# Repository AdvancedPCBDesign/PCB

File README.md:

# Advanced PCB Design (Group 15)

<a href="https://advancedpcbdesign.github.io/PCB/schematic.pdf"><strong>View Schematic (pdf) »</strong></a>

## KiCad Setup

### git

Execute in same directory as this README file

Before working on this project:
- `git pull`

See what's changed:
- `git status`

Commit and push changes:
- `git add *`
- `git commit -m "changes in ..."`
- `git push`

#### KiCAD JLCPCB tools
[https://github.com/bouni/kicad-jlcpcb-tools](https://github.com/bouni/kicad-jlcpcb-tools)

## Components Overview

| Concept                                         | Component             | Stock  | Price   | Link                                                                                                                                                                                                                                                                                                                                                                                                                                                                                                                                                                                                                                                                                                                                                                                                                                                                                                                                                                                                                                                                                                                                                                                                                                                                                                                                                              |
| ----------------------------------------------- | --------------------- | ------ | ------- | ----------------------------------------------------------------------------------------------------------------------------------------------------------------------------------------------------------------------------------------------------------------------------------------------------------------------------------------------------------------------------------------------------------------------------------------------------------------------------------------------------------------------------------------------------------------------------------------------------------------------------------------------------------------------------------------------------------------------------------------------------------------------------------------------------------------------------------------------------------------------------------------------------------------------------------------------------------------------------------------------------------------------------------------------------------------------------------------------------------------------------------------------------------------------------------------------------------------------------------------------------------------------------------------------------------------------------------------------------------------- |
| UV Sensor                                       | AS7331-AQFM           | 0      | $ 12.87 | [LCSC](https://www.lcsc.com/product-detail/C22457702.html) [Datasheet](https://www.lcsc.com/datasheet/C22457702.pdf)                                                                                                                                                                                                                                                                                                                                                                                                                                                                                                                                                                                                                                                                                                                                                                                                                                                                                                                                                                                                                                                                                                                                                                                                                                              |
| UV Sensor I2C                                   | LTR-390UV-01          | 0      | $ 3.37  | [JLCPCB](https://jlcpcb.com/partdetail/LiteOn-LTR_390UV01/C492374) [Datasheet](https://jlc-prod-smt.oss-eu-central-1.aliyuncs.com/smtDataManualFile/8588894290253004800-C492374.pdf?response-content-disposition=attachment%3B%20filename%3DC492374.pdf%3B%20filename%2A%3DUTF-8%27%27C492374.pdf&x-oss-date=20261022T112244Z&x-oss-expires=1800&x-oss-security-token=CAISgAN1q6Ft5B2yfSjIr5nRJvvBhrhH9oOcYUHngWMsf%2B1F3Z3fqTz2IHhMdHJsAOodtv0%2FmmhT6PkclqRLcbhpcmfjV%2BZHzLB8qfkBhX8%2F557b16cNrbH4M4H6aXeirtuwDsz9SNTCALjPD3nPii50x5bjaDymRCbLGJaViJlhHLN1Ow6jdmhpCctxLAlvo9NgFxm3D%2Fu2NQPwiWf9FVdhvhEG6Vly8qOi2MaRmFy8yFTx0b0SvJ%2BjYMrmPctoN9JnSdC5mfdzau3a1TJ84gRD0a5wkaVA1zbDs5bfISEIuUzebreLqY03dV4mOvdqIcMe8qigz88fk%2FfIioH6xyxKOexoSCnFTOiiupCcQLPyao9jLu6iayqViY7QaIOTqQohZmkAMwVOasAsI3Ngh4zF97Qt0cVNkXO9gWfLI8DtuMleWmrJ0EBmoaHD0eS19jklBdzSlusJRAJJUVBflCeKEaRNSAd3WGhEfM2%2BBt4QT30w5N2u00S8OSMIl8lOFKKWD5sagAFtcwKG348b1mUzBgtJh4%2BMkQ0MNsn9%2FxF2HpGh0Bm3%2BAHDdCkBsMSQTkxhfpKD557V3bFmR%2FM6RO7ja6TD2TNMN4imTTkpyuXGCddEgNZONk%2FHSSW0lGRNfjN74gcBhU2Y56%2FkgDQhi0Zqyy4%2BQfrkimxCRkldHE8glM%2BFpMkIFiAA&x-oss-signature-version=OSS4-HMAC-SHA256&x-oss-credential=STS.NZdmAukgfAAwcgVecysbi2XtK%2F20261022%2Feu-central-1%2Foss%2Faliyun_v4_request&x-oss-signature=278c7b70a0f79256bc8ae240f49d7be2213cf88d3748ce308f11e6cd0a1ca70c)      |
| UV Sensor I2C                                   | Si1133                | 0      | $ 2.74  | [JLCPCB](https://jlcpcb.com/partdetail/SKYWORKS_SILICONLABS-SI1133_AA00GM/C3678545)                                                                                                                                                                                                                                                                                                                                                                                                                                                                                                                                                                                                                                                                                                                                                                                                                                                                                                                                                                                                                                                                                                                                                                                                                                                                               |
| Co2 Sensor                                      | SCD40-D-R1            | 389    | $ 15.70 | [JLCPCB](https://jlcpcb.com/partdetail/Sensirion-SCD40_DR1/C3037696) [Datasheet](https://jlc-prod-smt.oss-eu-central-1.aliyuncs.com/smtDataManualFile/8589837130307973120-C3037696.pdf?response-content-disposition=attachment%3B%20filename%3DC3037696.pdf%3B%20filename%2A%3DUTF-8%27%27C3037696.pdf&x-oss-date=20261022T112435Z&x-oss-expires=1800&x-oss-security-token=CAISgAN1q6Ft5B2yfSjIr5nRJvvBhrhH9oOcYUHngWMsf%2B1F3Z3fqTz2IHhMdHJsAOodtv0%2FmmhT6PkclqRLcbhpcmfjV%2BZHzLB8qfkBhX8%2F557b16cNrbH4M4H6aXeirtuwDsz9SNTCALjPD3nPii50x5bjaDymRCbLGJaViJlhHLN1Ow6jdmhpCctxLAlvo9NgFxm3D%2Fu2NQPwiWf9FVdhvhEG6Vly8qOi2MaRmFy8yFTx0b0SvJ%2BjYMrmPctoN9JnSdC5mfdzau3a1TJ84gRD0a5wkaVA1zbDs5bfISEIuUzebreLqY03dV4mOvdqIcMe8qigz88fk%2FfIioH6xyxKOexoSCnFTOiiupCcQLPyao9jLu6iayqViY7QaIOTqQohZmkAMwVOasAsI3Ngh4zF97Qt0cVNkXO9gWfLI8DtuMleWmrJ0EBmoaHD0eS19jklBdzSlusJRAJJUVBflCeKEaRNSAd3WGhEfM2%2BBt4QT30w5N2u00S8OSMIl8lOFKKWD5sagAFtcwKG348b1mUzBgtJh4%2BMkQ0MNsn9%2FxF2HpGh0Bm3%2BAHDdCkBsMSQTkxhfpKD557V3bFmR%2FM6RO7ja6TD2TNMN4imTTkpyuXGCddEgNZONk%2FHSSW0lGRNfjN74gcBhU2Y56%2FkgDQhi0Zqyy4%2BQfrkimxCRkldHE8glM%2BFpMkIFiAA&x-oss-signature-version=OSS4-HMAC-SHA256&x-oss-credential=STS.NZdmAukgfAAwcgVecysbi2XtK%2F20261022%2Feu-central-1%2Foss%2Faliyun_v4_request&x-oss-signature=192cf8a0d5a21bb1fca0288a9b8ef685442e7d2fc05deb0e38e5b62fed935ffc) |
| gas, pressure, temperature & humidity<br>sensor | BME680                | 372    | $ 10.86 | [JLCPCB](https://jlcpcb.com/partdetail/BoschSensortec-BME680/C125972) [Datasheet](https://jlc-prod-smt.oss-eu-central-1.aliyuncs.com/smtDataManualFile/8588886842028122112-C125972.pdf?response-content-disposition=attachment%3B%20filename%3DC125972.pdf%3B%20filename%2A%3DUTF-8%27%27C125972.pdf&x-oss-date=20261021T151906Z&x-oss-expires=1800&x-oss-security-token=CAISgAN1q6Ft5B2yfSjIr5mCf8%2FaupxQhLPSR0PwkFIwSsdZuKDbkjz2IHhMdHJsAOodtv0%2FmmhT6PkclqRLcbhpcmfjV%2BZHzLB8qZYVtxg8557b16cNrbH4M4H6aXeirtuwDsz9SNTCALjPD3nPii50x5bjaDymRCbLGJaViJlhHLN1Ow6jdmhpCctxLAlvo9NgFxm3D%2Fu2NQPwiWf9FVdhvhEG6Vly8qOi2MaRmFy8yFTx0b0SvJ%2BjYMrmPctoN9JnSdC5mfdzau3a1TJ84gRD0a5wkaVA1zbDs5bfISEIuUzebreLqY03dV4mOvdqIcMe8qigz88fk%2FfIioH6xyxKOexoSCnFTOiiupCcQLPyao9jLu6iayqViY7QaIOTqQohZmkAMwVOasAsI3Ngh4zF97Qt0cVNkXO9gWfLI8DtuMleWgqmD8h7waHD0eS19jklBdzSlusJRAJJUVBflCeKEaRNSAd3WGhEfM2%2BBt4QT30w5N2u00S8OSMIJCdatqKWD5sagAEv7ngkOgawgwfiUHBX47YDcRBsRJt1XfKQ06GKLNxnRZIJmWZTwc55WEkmHm69WrZcaDtwaaN51Z9kWhH1cAPyDc6chX00A9ff2085vDMjgJllAMLDfzRuJBN82j6JOFTTuQiaDRPYa2AWHEQ4EVaGZsqWWgurQIq0EPFC1YsBqiAA&x-oss-signature-version=OSS4-HMAC-SHA256&x-oss-credential=STS.NZ74unWCq3q9EeAtReFHuWepp%2F20261021%2Feu-central-1%2Foss%2Faliyun_v4_request&x-oss-signature=7137659a65947dfa91fdfa0ecc3feda6760c6ecd1cf832c23a8c38a2930725ed)                     |
| SPI Digital to Analog Converters (DAC)          | MCP4822-E/SN          | 2,766  | $ 2.37  | [JLCPCB](https://jlcpcb.com/partdetail/MicrochipTech-MCP4822_ESN/C16040) [Datasheet](https://jlc-prod-smt.oss-eu-central-1.aliyuncs.com/smtDataManualFile/8588882123877470208-C16040.pdf?response-content-disposition=attachment%3B%20filename%3DC16040.pdf%3B%20filename%2A%3DUTF-8%27%27C16040.pdf&x-oss-date=20261022T112911Z&x-oss-expires=1800&x-oss-security-token=CAISgAN1q6Ft5B2yfSjIr5nRJvvBhrhH9oOcYUHngWMsf%2B1F3Z3fqTz2IHhMdHJsAOodtv0%2FmmhT6PkclqRLcbhpcmfjV%2BZHzLB8qfkBhX8%2F557b16cNrbH4M4H6aXeirtuwDsz9SNTCALjPD3nPii50x5bjaDymRCbLGJaViJlhHLN1Ow6jdmhpCctxLAlvo9NgFxm3D%2Fu2NQPwiWf9FVdhvhEG6Vly8qOi2MaRmFy8yFTx0b0SvJ%2BjYMrmPctoN9JnSdC5mfdzau3a1TJ84gRD0a5wkaVA1zbDs5bfISEIuUzebreLqY03dV4mOvdqIcMe8qigz88fk%2FfIioH6xyxKOexoSCnFTOiiupCcQLPyao9jLu6iayqViY7QaIOTqQohZmkAMwVOasAsI3Ngh4zF97Qt0cVNkXO9gWfLI8DtuMleWmrJ0EBmoaHD0eS19jklBdzSlusJRAJJUVBflCeKEaRNSAd3WGhEfM2%2BBt4QT30w5N2u00S8OSMIl8lOFKKWD5sagAFtcwKG348b1mUzBgtJh4%2BMkQ0MNsn9%2FxF2HpGh0Bm3%2BAHDdCkBsMSQTkxhfpKD557V3bFmR%2FM6RO7ja6TD2TNMN4imTTkpyuXGCddEgNZONk%2FHSSW0lGRNfjN74gcBhU2Y56%2FkgDQhi0Zqyy4%2BQfrkimxCRkldHE8glM%2BFpMkIFiAA&x-oss-signature-version=OSS4-HMAC-SHA256&x-oss-credential=STS.NZdmAukgfAAwcgVecysbi2XtK%2F20261022%2Feu-central-1%2Foss%2Faliyun_v4_request&x-oss-signature=da09d3dfd41b7500104f980c4a8122f00df30e5c8309194bcfaddede4794e755)   |
| Display (7 segment, 4 digits)                   | FJ5461AH Orange-red   | 4,645  | $ 0.63  | [JLCPCB](https://jlcpcb.com/partdetail/11253-FJ5461AH_Orangered/C10709) [Datasheet](https://jlc-prod-smt.oss-eu-central-1.aliyuncs.com/smtDataManualFile/8588886982025601024-C10709.pdf?response-content-disposition=attachment%3B%20filename%3DC10709.pdf%3B%20filename%2A%3DUTF-8%27%27C10709.pdf&x-oss-date=20261021T145839Z&x-oss-expires=1800&x-oss-security-token=CAISgAN1q6Ft5B2yfSjIr5mCf8%2FaupxQhLPSR0PwkFIwSsdZuKDbkjz2IHhMdHJsAOodtv0%2FmmhT6PkclqRLcbhpcmfjV%2BZHzLB8qZYVtxg8557b16cNrbH4M4H6aXeirtuwDsz9SNTCALjPD3nPii50x5bjaDymRCbLGJaViJlhHLN1Ow6jdmhpCctxLAlvo9NgFxm3D%2Fu2NQPwiWf9FVdhvhEG6Vly8qOi2MaRmFy8yFTx0b0SvJ%2BjYMrmPctoN9JnSdC5mfdzau3a1TJ84gRD0a5wkaVA1zbDs5bfISEIuUzebreLqY03dV4mOvdqIcMe8qigz88fk%2FfIioH6xyxKOexoSCnFTOiiupCcQLPyao9jLu6iayqViY7QaIOTqQohZmkAMwVOasAsI3Ngh4zF97Qt0cVNkXO9gWfLI8DtuMleWgqmD8h7waHD0eS19jklBdzSlusJRAJJUVBflCeKEaRNSAd3WGhEfM2%2BBt4QT30w5N2u00S8OSMIJCdatqKWD5sagAEv7ngkOgawgwfiUHBX47YDcRBsRJt1XfKQ06GKLNxnRZIJmWZTwc55WEkmHm69WrZcaDtwaaN51Z9kWhH1cAPyDc6chX00A9ff2085vDMjgJllAMLDfzRuJBN82j6JOFTTuQiaDRPYa2AWHEQ4EVaGZsqWWgurQIq0EPFC1YsBqiAA&x-oss-signature-version=OSS4-HMAC-SHA256&x-oss-credential=STS.NZ74unWCq3q9EeAtReFHuWepp%2F20261021%2Feu-central-1%2Foss%2Faliyun_v4_request&x-oss-signature=a97a1d39f0bcf64231552073ed21d197983a9516be7a86cf6a5715432c7a60e9)                      |
| RGB LED                                         | 61-238/RSGCBKC-B02/ET | 34,253 | $ 0.22  | [JLCPCB](https://jlcpcb.com/partdetail/EverlightElec-61_238_RSGCBKC_B02ET/C111658) [Datasheet](https://www.everlighteurope.com/custom/files/datasheets/DSE-0008393.pdf)                                                                                                                                                                                                                                                                                                                                                                                                                                                                                                                                                                                                                                                                                                                                                                                                                                                                                                                                                                                                                                                                                                                                                                                           |
| 5V Buck                                         | AP63205WU-7           | 43,000 | $ 0.44  | [JLCPCB](https://jlcpcb.com/parts/componentSearch?searchTxt=ap63205wu-7) [Datasheet](https://jlc-prod-smt.oss-eu-central-1.aliyuncs.com/smtDataManualFile/8560085326519181312-C2071056.pdf?response-content-disposition=attachment%3B%20filename%3DC2071056.pdf%3B%20filename%2A%3DUTF-8%27%27C2071056.pdf&x-oss-date=20261026T150132Z&x-oss-expires=3600&x-oss-security-token=CAISgAN1q6Ft5B2yfSjIr5nhLM%2FatJNF8IG9a0TZqVRhfcEVqKyclTz2IHhMdHJsAOodtv0%2FmmhT6PkclqRLcbhpcmfjV%2BZHzLB8qbAz1So%2B557b16cNrbH4M4H6aXeirtuwDsz9SNTCALjPD3nPii50x5bjaDymRCbLGJaViJlhHLN1Ow6jdmhpCctxLAlvo9NgFxm3D%2Fu2NQPwiWf9FVdhvhEG6Vly8qOi2MaRmFy8yFTx0b0SvJ%2BjYMrmPctoN9JnSdC5mfdzau3a1TJ84gRD0a5wkaVA1zbDs5bfISEIuUzebreLqY03dV4mOvdqIcMe8qigz88fk%2FfIioH6xyxKOexoSCnFTOiiupCcQLPyao9jLu6iayqViY7QaIOTqQohZmkAMwVOasAsI3Ngh4zF97Qt0cVNkXO9gWfLI8DtuMleWkpgx8RRfJSgc5lCkRRYwGs1287ugXlSQzo890KPDAEovaKCnZ2ZSfh7Y4sNknI6i%2Bfc2Se2MIkI0Ves6KKWD5sagAETkvmy7h9OYoFAvdr7axrdKwjcHAMKQh3YtnyonJmWnSdQx6P54oaTjRFjQ%2FVclanVo2s3pI6zJkwOxHC0PabYRlplZQCzaIl%2BSlBYuEkAuNP5Av9X4ZJpDJ1Dc7Cw98tb0j13u2nTfEVD6xHmORe7dKZ4RUd43DGXn6wu%2BZzqlCAA&x-oss-signature-version=OSS4-HMAC-SHA256&x-oss-credential=STS.NZTgunYLdGCVibhMT4qN9Gi7w%2F20261026%2Feu-central-1%2Foss%2Faliyun_v4_request&x-oss-signature=107ef51ac143ffa4f46a59c67b2ca34b03d67cd8c8dcfc19fb7dea56f4a51d6d)       |                                                                                                                                                                                                                                                                                                                                                                                                                                                                                                                                                                                                                                                                                                                                                                                                                                                                                                                                                                                                                                                                                                                                                                                   |
| Linearregler  3,3V                              | NCP1117ST33T3G        | 112,771| $ 0.21  | [JLCPCB](https://jlcpcb.com/partdetail/onsemi-NCP1117ST33T3G/C26537) [Datasheet](https://jlc-prod-smt.oss-eu-central-1.aliyuncs.com/smtDataManualFile/8586175789088329728-C26537.pdf?response-content-disposition=attachment%3B%20filename%3DC26537.pdf%3B%20filename%2A%3DUTF-8%27%27C26537.pdf&x-oss-date=20261026T150355Z&x-oss-expires=1800&x-oss-security-token=CAISgAN1q6Ft5B2yfSjIr5nhLM%2FatJNF8IG9a0TZqVRhfcEVqKyclTz2IHhMdHJsAOodtv0%2FmmhT6PkclqRLcbhpcmfjV%2BZHzLB8qbAz1So%2B557b16cNrbH4M4H6aXeirtuwDsz9SNTCALjPD3nPii50x5bjaDymRCbLGJaViJlhHLN1Ow6jdmhpCctxLAlvo9NgFxm3D%2Fu2NQPwiWf9FVdhvhEG6Vly8qOi2MaRmFy8yFTx0b0SvJ%2BjYMrmPctoN9JnSdC5mfdzau3a1TJ84gRD0a5wkaVA1zbDs5bfISEIuUzebreLqY03dV4mOvdqIcMe8qigz88fk%2FfIioH6xyxKOexoSCnFTOiiupCcQLPyao9jLu6iayqViY7QaIOTqQohZmkAMwVOasAsI3Ngh4zF97Qt0cVNkXO9gWfLI8DtuMleWkpgx8RRfJSgc5lCkRRYwGs1287ugXlSQzo890KPDAEovaKCnZ2ZSfh7Y4sNknI6i%2Bfc2Se2MIkI0Ves6KKWD5sagAETkvmy7h9OYoFAvdr7axrdKwjcHAMKQh3YtnyonJmWnSdQx6P54oaTjRFjQ%2FVclanVo2s3pI6zJkwOxHC0PabYRlplZQCzaIl%2BSlBYuEkAuNP5Av9X4ZJpDJ1Dc7Cw98tb0j13u2nTfEVD6xHmORe7dKZ4RUd43DGXn6wu%2BZzqlCAA&x-oss-signature-version=OSS4-HMAC-SHA256&x-oss-credential=STS.NZTgunYLdGCVibhMT4qN9Gi7w%2F20261026%2Feu-central-1%2Foss%2Faliyun_v4_request&x-oss-signature=706c27bc0812f032ab16e95ca696319d2e6fa5477858ed2f9ec250c9d9df3820)                 |
| NTC-10k                                  | NT08104F3950B1F       |   13     |    $0.24     |   [jlcpcb](https://jlcpcb.com/partdetail/EATON-NT08104F3950B1F/C17254494)   |
| DAC i2C 10-Bit                                  | MCP4716A0T-E/CH       |        |         |      |

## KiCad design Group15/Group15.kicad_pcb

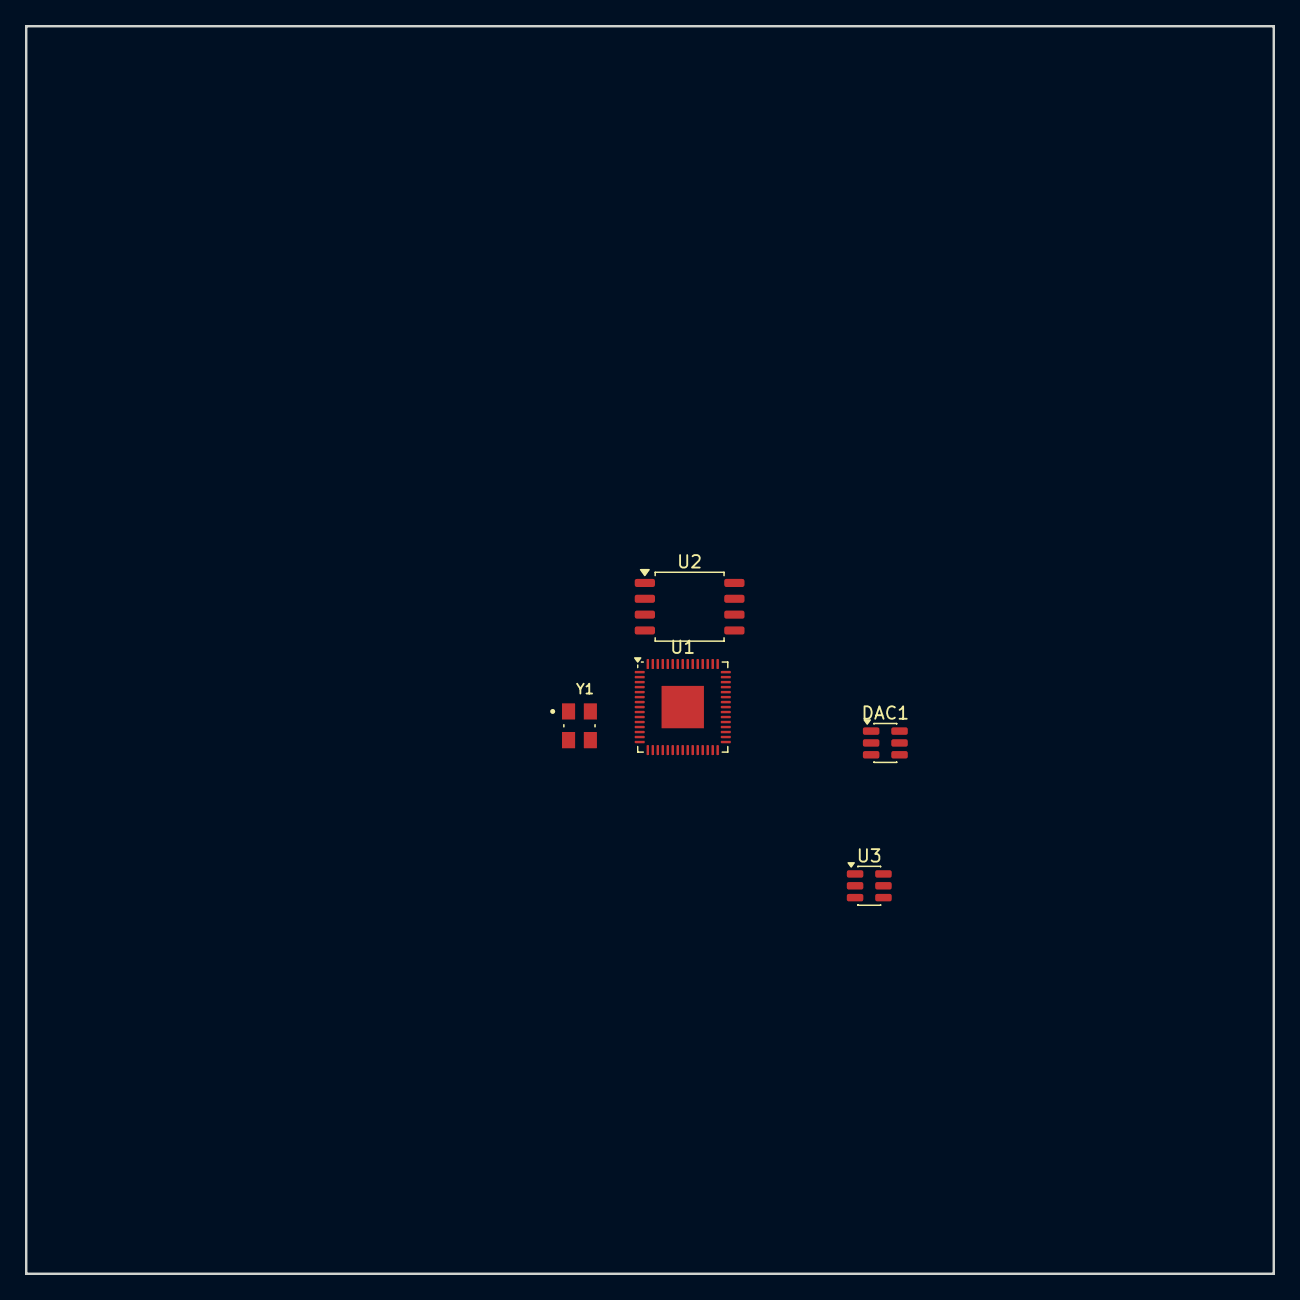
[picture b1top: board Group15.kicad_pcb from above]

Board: 4 copper layers, 100.0 x 100.0 mm, 5 parts (0 on the bottom side), 10 nets, no tracks yet.

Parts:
DAC1: SOT-23-6
U1: RP2350A; QFN-60-1EP_7x7mm_P0.4mm_EP3.4x3.4mm
U2: W25Q128JVS; SOIC-8_5.3x5.3mm_P1.27mm
U3: AP63205WU; TSOT-23-6
Y1: ABM8-272-T3; XTAL_ABM8-272-T3

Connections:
+3V3: U1.2 (GPIO0), U2.1 (~CS), U2.8 (VCC)
/RP2350A/QSPI_SCLK: U1.56 (QSPI_SCLK), U2.6 (CLK)
/RP2350A/QSPI_SD0: U1.57 (QSPI_SD0), U2.5 (DI/IO_{0})
/RP2350A/QSPI_SD1: U1.59 (QSPI_SD1), U2.2 (DO/IO_{1})
/RP2350A/QSPI_SD2: U1.58 (QSPI_SD2), U2.3 (~WP/IO_{2})
/RP2350A/QSPI_SD3: U1.55 (QSPI_SD3), U2.7 (~HOLD/~RESET/IO_{3})
/RP2350A/XIN: U1.21 (XIN), Y1.1
GND: DAC1.2 (Vss), U2.4 (GND), Y1.2 (GND), Y1.4 (GND__1)
unnamed: U1.6 (DVDD), U1.23 (DVDD), U1.39 (DVDD)
unnamed: U1.1 (IOVDD), U1.11 (IOVDD), U1.20 (IOVDD), U1.30 (IOVDD), U1.38 (IOVDD), U1.45 (IOVDD)
